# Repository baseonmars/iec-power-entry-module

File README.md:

# Universal IEC Power Inlet with Voltage Surge and Current Inrush Limiting

I find myself needing a power entry solution when working on amps and other audio related equipment with linear power supplies.

This is my attempt at creating a reusable board

## Features

- IEC C14 socket
- Dual fuse holder
- Power switch
- Voltage selection for US and EU voltages when using a dual primary transformer
- MOV for voltage surge suppression
- NTC thermistor for current inrush limiting

## Bill of Materials

- Schurter DC21 power inlet with power switch
- Schurter 4301.1405 fuse drawer
- V&K V80212MS02Q voltage selector switch
- MOVs 7.5mm pitch, max diameter 12mm, max width 5mm \*
- EPCOS / TDK Inrush Current limiter\* pitch 7.5mm, max diameter 12mm, max width 7mm

* You must select an adequate voltage and inrush limiter for your target application.

## Safety Note

This schematic and associated designs and files are provided without any guarentee of safety. Please do your research and use at your own risk.

This is very much a work in progress - this notice will be removed when I have greater confidence in the design.

## Preview

## Things and of note

This design in heavily inspirited by [Pete Millett's](https://www.pmillett.com) NuClassD power supply - Please check out his work and consider buying from him.

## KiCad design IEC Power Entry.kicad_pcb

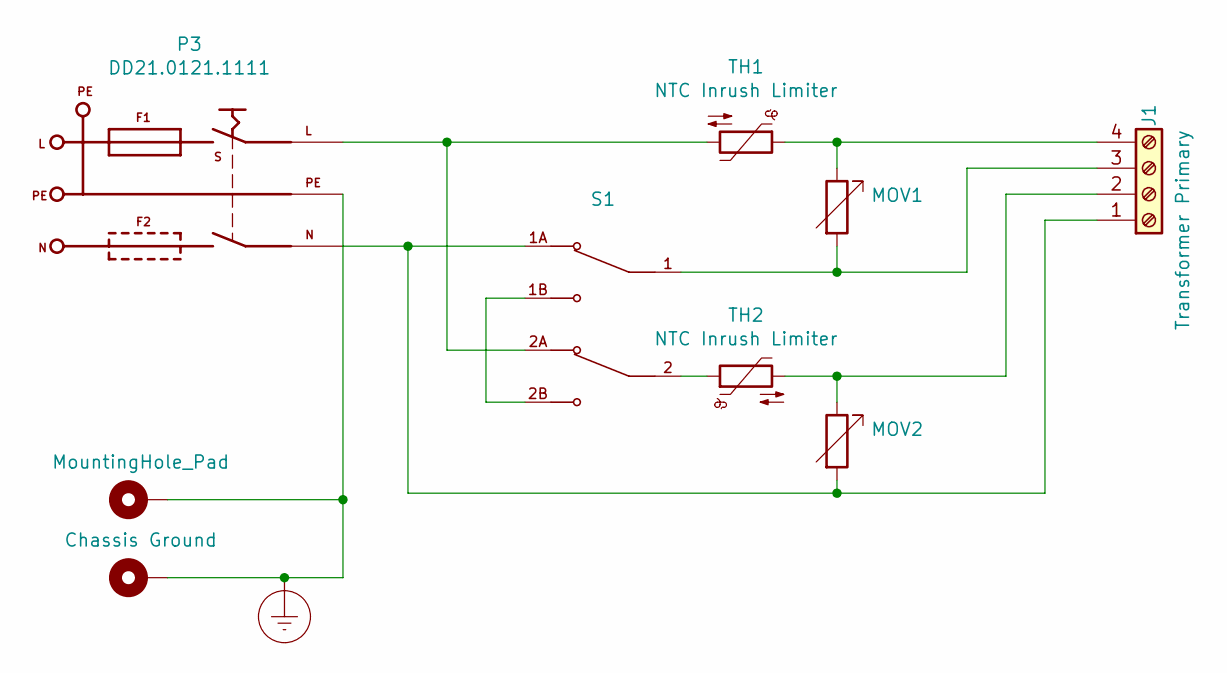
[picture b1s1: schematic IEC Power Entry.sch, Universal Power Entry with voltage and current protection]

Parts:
J1: Transformer Primary; TerminalBlock_TE-1546062-4_1x04_P7.50mm_Horizontal
MOV1, MOV2: MOV; RV_Disc_D12mm_W5mm_P7.5mm
P1: MountingHole_Pad; MountingHole_3.5mm_Pad
P2: Chassis Ground; MountingHole_3.5mm_Pad
P3: DD21.0121.1111; SCHURTER-DD21.0121.1111
S1: V80212MS02Q; SW_V80212MS02Q
TH1, TH2: NTC Inrush Limiter; RV_Disc_D12mm_W7.1mm_P7.5mm

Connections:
Earth_Protective: P1.1, P2.1, P3.PE
unnamed: J1.1, MOV2.2, P3.N, S1.1A
unnamed: J1.2, MOV2.1, TH2.2
unnamed: J1.3, MOV1.2, S1.1
unnamed: J1.4, MOV1.1, TH1.1
unnamed: P3.L, S1.2A, TH1.2
unnamed: S1.1B, S1.2B
unnamed: S1.2, TH2.1

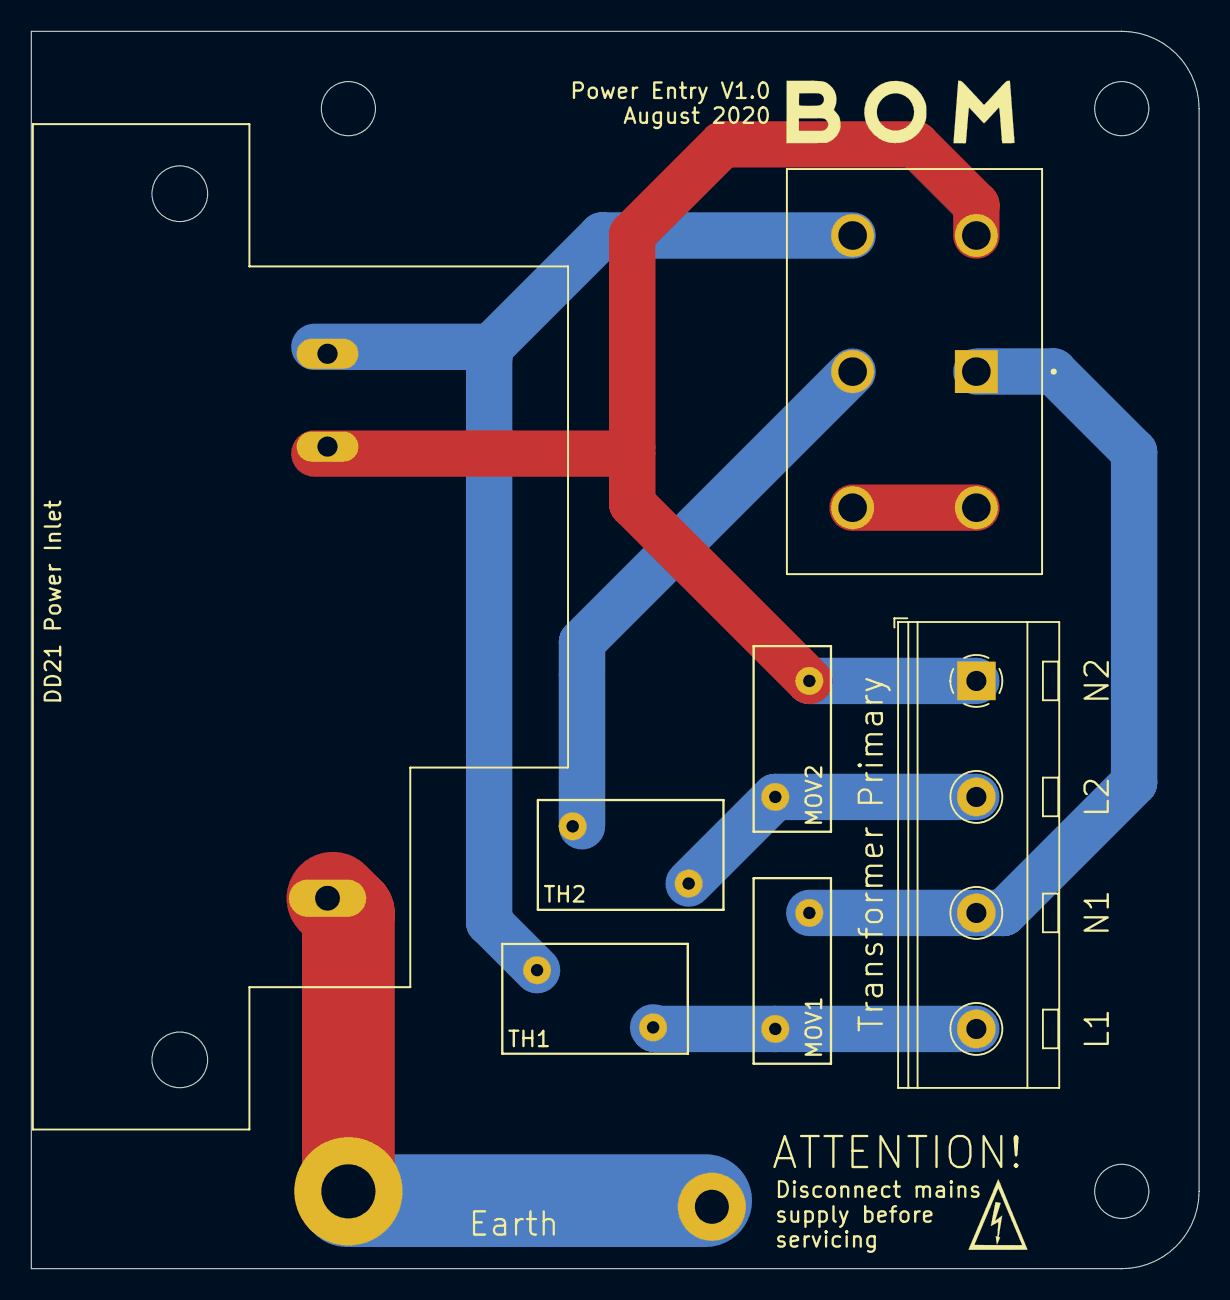
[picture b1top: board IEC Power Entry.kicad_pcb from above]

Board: 2 copper layers, 75.5 x 80.0 mm, 9 parts (0 on the bottom side), 8 nets.

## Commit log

2020-08-18 chore: add fp-lib-table
2020-08-18 feat: add Gerber files for 1.0.a
2020-08-18 docs: add screenshot to README
2020-08-19 fix: correct mov and inrush placement
2020-08-23 various updates to track widths and footprints
2020-08-23 chore: increase gaps to meet DIN EN 60664-1 (cat. II) and 230VAC
2020-08-26 feat: more track layout tweaking
2020-08-26 docs: small updates to components
2020-08-26 feat: add warning marks + silkscreen alignment
2020-08-27 fix: adjust hole spacing for 70x50mm
2020-08-27 fix: tweak edge of board so that power module is flush
2020-08-27 chore: reapply clearance settings for board
